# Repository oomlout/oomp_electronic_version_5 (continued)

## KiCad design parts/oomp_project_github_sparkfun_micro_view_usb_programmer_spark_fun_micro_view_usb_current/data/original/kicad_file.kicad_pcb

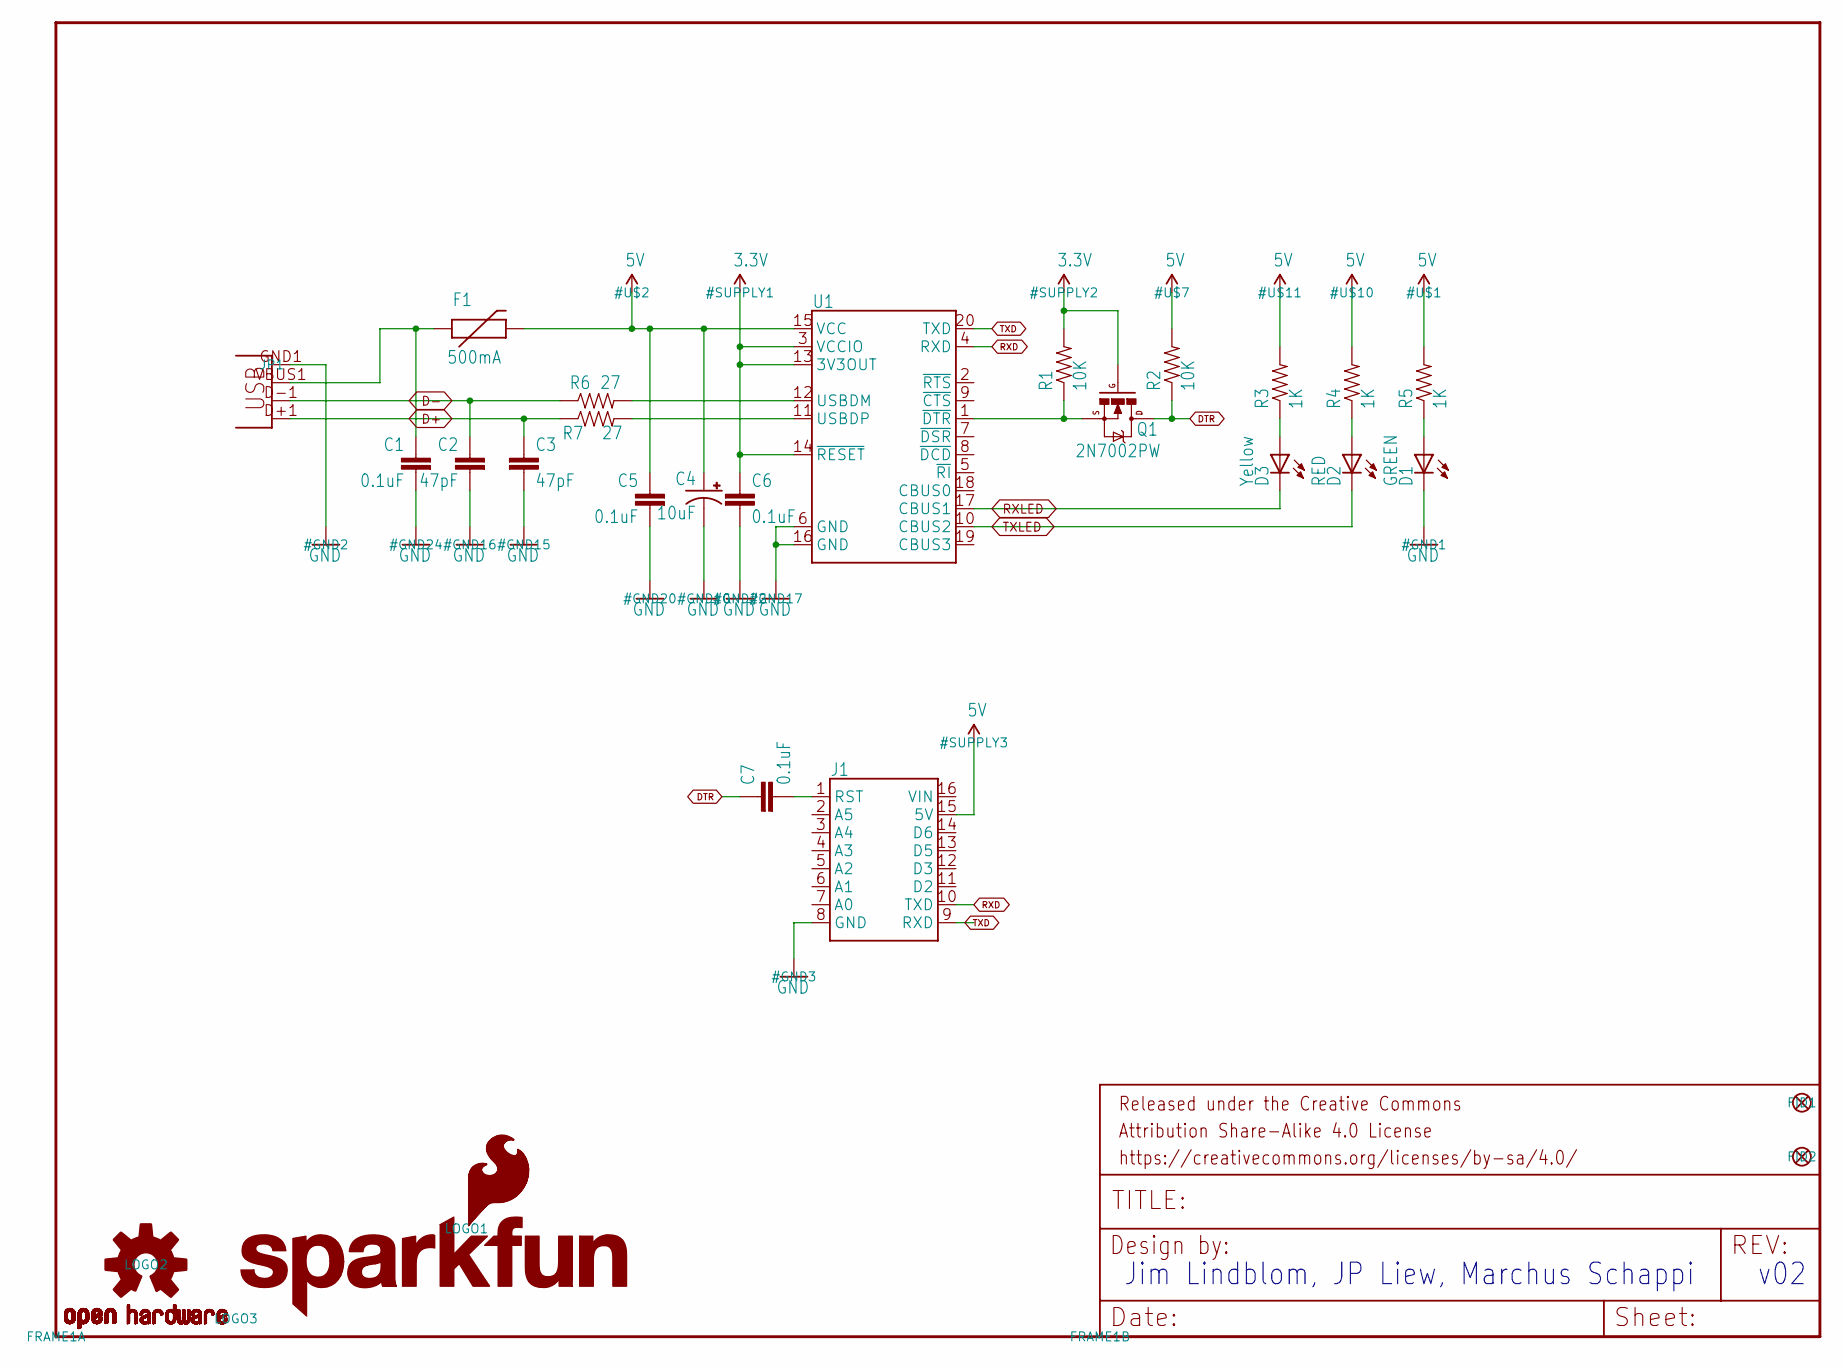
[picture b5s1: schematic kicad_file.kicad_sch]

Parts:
C1, C5, C6, C7: 0.1uF; 0603-CAP
C2, C3: 47pF; 0603-CAP
C4: 10uF; EIA3216
D1: GREEN; LED-1206
D2: RED; LED-1206
D3: Yellow; LED-1206
F1: 500mA; PTC-1206-WIDE
FID1, FID2: FIDUCIAL1X2; FIDUCIAL-1X2
FRAME1: FRAME-LETTER; CREATIVE_COMMONS
J1: MICROVIEW-16ND; MV-DIP16-NODIMENSION
JP1: USBA-SMD-MALE; USB-A-SMT-MALE
LOGO1: SFE_LOGO_FLAME.1_INCH; SFE_LOGO_FLAME_.1
LOGO2: OSHW-LOGOS; OSHW-LOGO-S
LOGO3: SFE_LOGO_NAME_FLAME.1_INCH; SFE_LOGO_NAME_FLAME_.1
Q1: 2N7002PW; SOT323
R1, R2: 10K; 0603-RES
R3, R4, R5: 1K; 0603-RES
R6, R7: 27; 0603-RES
U1: FT231XS; SSOP20_L

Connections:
3.3V: C6.1, Q1.1 (G), R1.2, U1.3 (VCCIO), U1.13 (3V3OUT), U1.14 (~RESET)
5V: C4.A (+), C5.1, F1.2, J1.15 (5V), R2.2, R3.2, R4.2, R5.2, U1.15 (VCC)
D+: C3.1, JP1.D+1 (D+), R7.1
D-: C2.1, JP1.D-1 (D-), R6.1
DTR: C7.1, Q1.3 (D), R2.1
GND: C1.2, C2.2, C3.2, C4.C (-), C5.2, C6.2, D1.C, J1.8 (GND), JP1.GND1 (GND), U1.6 (GND), U1.16 (GND)
unnamed: D1.A, R5.1
unnamed: C7.2, J1.1 (RST)
unnamed: R6.2, U1.12 (USBDM)
unnamed: R7.2, U1.11 (USBDP)
unnamed: D2.A, R4.1
unnamed: D3.A, R3.1
unnamed: Q1.2 (S), R1.1, U1.1 (~DTR)
RXD: J1.10 (TXD), U1.4 (RXD)
RXLED: D3.C, U1.17 (CBUS1)
TXD: J1.9 (RXD), U1.20 (TXD)
TXLED: D2.C, U1.10 (CBUS2)
VUSB: C1.1, F1.1, JP1.VBUS1 (VBUS)

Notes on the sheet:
v02
Jim Lindblom, JP Liew, Marchus Schappi

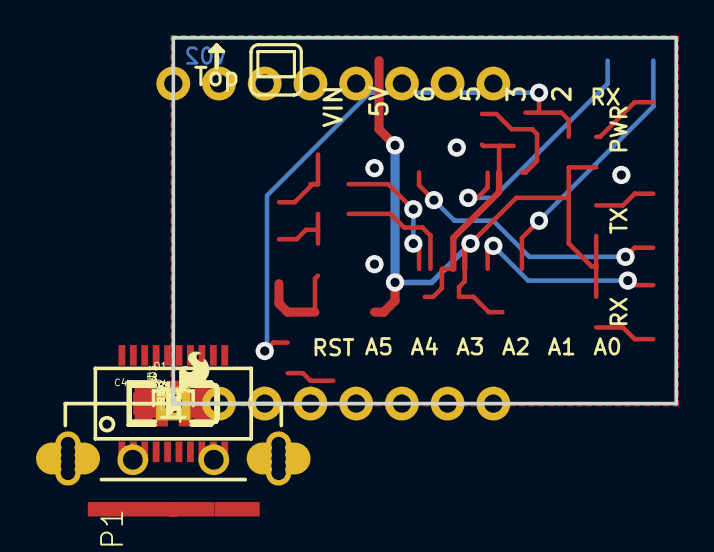
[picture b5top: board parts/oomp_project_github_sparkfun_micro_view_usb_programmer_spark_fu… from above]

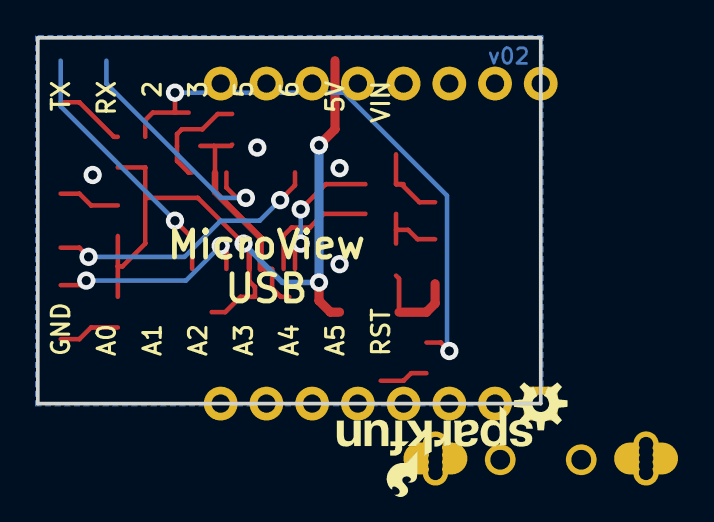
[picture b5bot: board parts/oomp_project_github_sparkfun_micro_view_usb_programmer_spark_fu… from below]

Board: 2 copper layers, 27.9 x 20.3 mm, 28 parts (2 on the bottom side), 18 nets.

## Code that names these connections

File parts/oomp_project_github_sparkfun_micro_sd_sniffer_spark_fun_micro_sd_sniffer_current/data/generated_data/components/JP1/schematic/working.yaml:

available: true
units:
- reference: JP1
  source_file: data/kicad_file.kicad_sch
  uuid: b0a12182-e892-46df-93f5-0551e3f96d0f
  library_id: kicad_file-eagle-import:M08
  unit: 1
  body_style: 1
  position:
    x: 144.78
    y: 99.06
    rotation: 0.0
    mirror: null
    units: mm
  properties:
    Reference: JP1
    Value: M08
    Footprint: kicad_file:1X08
    Datasheet: ''
    Description: ''
  in_bom: true
  on_board: true
  in_position_files: true
  dnp: false
  pins:
  - number: '1'
    name: '1'
    electrical_type: passive
    graphic_style: line
    local_position:
      x: 5.08
      y: -7.62
      rotation: 180.0
    length: 5.08
    position:
      x: 149.86
      y: 106.68
    net: DAT2
    net_aliases:
    - DAT2
    net_scope: global
    no_connect: false
    connected_to:
    - reference: U1
      pin_number: DAT2
      pin_name: DAT2
    - reference: U2
      pin_number: '1'
      pin_name: NC
  - number: '2'
    name: '2'
    electrical_type: passive
    graphic_style: line
    local_position:
      x: 5.08
      y: -5.08
      rotation: 180.0
    length: 5.08
    position:
      x: 149.86
      y: 104.14
    net: CD/DAT3
    net_aliases:
    - CD/DAT3
    net_scope: global
    no_connect: false
    connected_to:
    - reference: U1
      pin_number: CD/DAT3
      pin_name: CD/DAT3
    - reference: U2
      pin_number: '2'
      pin_name: CS
  - number: '3'
    name: '3'
    electrical_type: passive
    graphic_style: line
    local_position:
      x: 5.08
      y: -2.54
      rotation: 180.0
    length: 5.08
    position:
      x: 149.86
      y: 101.6
    net: CMD
    net_aliases:
    - CMD
    net_scope: global
    no_connect: false
    connected_to:
    - reference: U1
      pin_number: CMD
      pin_name: CMD
    - reference: U2
      pin_number: '3'
      pin_name: DI
  - number: '4'
    name: '4'
    electrical_type: passive
    graphic_style: line
    local_position:
      x: 5.08
      y: 0.0
      rotation: 180.0
    length: 5.08
    position:
      x: 149.86
      y: 99.06
    net: GND
    net_aliases:
    - GND
    net_scope: global
    no_connect: false
    connected_to:
    - reference: '#GND1'
      pin_number: '1'
      pin_name: GND
    - reference: '#GND2'
      pin_number: '1'
      pin_name: GND
    - reference: '#GND3'
      pin_number: '1'
      pin_name: GND
    - reference: U1
      pin_number: GND
      pin_name: GND
    - reference: U2
      pin_number: '6'
      pin_name: GND
    - reference: U2
      pin_number: CD1
      pin_name: CD1
    - reference: U2
      pin_number: CD2
      pin_name: CD2
    - reference: U2
      pin_number: GND1
      pin_name: SHIELD
    - reference: U2
      pin_number: GND3
      pin_name: SHIELD
  - number: '5'
    name: '5'
    electrical_type: passive
    graphic_style: line
    local_position:
      x: 5.08
      y: 2.54
      rotation: 180.0
    length: 5.08
    position:
      x: 149.86
      y: 96.52
    net: VCC
    net_aliases:
    - VCC
    net_scope: global
    no_connect: false
    connected_to:
    - reference: '#SUPPLY1'
      pin_number: '1'
      pin_name: VCC
    - reference: '#SUPPLY2'
      pin_number: '1'
      pin_name: VCC
    - reference: '#SUPPLY3'
      pin_number: '1'
      pin_name: VCC
    - reference: U1
      pin_number: VCC
      pin_name: VDD
    - reference: U2
      pin_number: '4'
      pin_name: VCC
  - number: '6'
    name: '6'
    electrical_type: passive
    graphic_style: line
    local_position:
      x: 5.08
      y: 5.08
      rotation: 180.0
    length: 5.08
    position:
      x: 149.86
      y: 93.98
    net: CLK
    net_aliases:
    - CLK
    net_scope: global
    no_connect: false
    connected_to:
    - reference: U1
      pin_number: CLK
      pin_name: CLK
    - reference: U2
      pin_number: '5'
      pin_name: SCK
  - number: '7'
    name: '7'
    electrical_type: passive
    graphic_style: line
    local_position:
      x: 5.08
      y: 7.62
      rotation: 180.0
    length: 5.08
    position:
      x: 149.86
      y: 91.44
    net: DAT0
    net_aliases:
    - DAT0
    net_scope: global
    no_connect: false
    connected_to:
    - reference: U1
      pin_number: DAT0
      pin_name: DAT0
    - reference: U2
      pin_number: '7'
      pin_name: DO
  - number: '8'
    name: '8'
    electrical_type: passive
    graphic_style: line
    local_position:
      x: 5.08
      y: 10.16
      rotation: 180.0
    length: 5.08
    position:
      x: 149.86
      y: 88.9
    net: DAT1
    net_aliases:
    - DAT1
    net_scope: global
    no_connect: false
    connected_to:
    - reference: U1
      pin_number: DAT1
      pin_name: DAT1
    - reference: U2
      pin_number: '8'
      pin_name: RSV
  size:
    local_graphics:
      measurement: symbol graphics only; excludes pins, properties, and text
      units: mm
      available: true
      min:
        x: -5.2832
        y: -10.3632
      max:
        x: 1.4732
        y: 12.9032
      width: 6.7564
      height: 23.2664
      center:
        x: -1.905
        y: 1.27
    placed_graphics:
      measurement: axis-aligned bounds after schematic placement, rotation, and mirroring
      units: mm
      available: true
      min:
        x: 139.4968
        y: 86.1568
      max:
        x: 146.2532
        y: 109.4232
      width: 6.7564
      height: 23.2664
      center:
        x: 142.875
        y: 97.79
  warnings: []
connected_components:
- reference: '#GND1'
  pin_number: '1'
  pin_name: GND
- reference: '#GND2'
  pin_number: '1'
  pin_name: GND
- reference: '#GND3'
  pin_number: '1'
  pin_name: GND
- reference: '#SUPPLY1'
  pin_number: '1'
  pin_name: VCC
- reference: '#SUPPLY2'
  pin_number: '1'
  pin_name: VCC
- reference: '#SUPPLY3'
  pin_number: '1'
  pin_name: VCC
- reference: U1
  pin_number: CD/DAT3
  pin_name: CD/DAT3
- reference: U1
  pin_number: CLK
  pin_name: CLK
- reference: U1
  pin_number: CMD
  pin_name: CMD
- reference: U1
  pin_number: DAT0
  pin_name: DAT0
- reference: U1
  pin_number: DAT1
  pin_name: DAT1
- reference: U1
  pin_number: DAT2
  pin_name: DAT2
- reference: U1
  pin_number: GND
  pin_name: GND
- reference: U1
  pin_number: VCC
  pin_name: VDD
- reference: U2
  pin_number: '1'
  pin_name: NC
- reference: U2
  pin_number: '2'
  pin_name: CS
- reference: U2
  pin_number: '3'
  pin_name: DI
- reference: U2
  pin_number: '4'
  pin_name: VCC
- reference: U2
  pin_number: '5'
  pin_name: SCK
- reference: U2
  pin_number: '6'
  pin_name: GND
- reference: U2
  pin_number: '7'
  pin_name: DO
- reference: U2
  pin_number: '8'
  pin_name: RSV
- reference: U2
  pin_number: CD1
  pin_name: CD1
- reference: U2
  pin_number: CD2
  pin_name: CD2
- reference: U2
  pin_number: GND1
  pin_name: SHIELD
- reference: U2
  pin_number: GND3
  pin_name: SHIELD
